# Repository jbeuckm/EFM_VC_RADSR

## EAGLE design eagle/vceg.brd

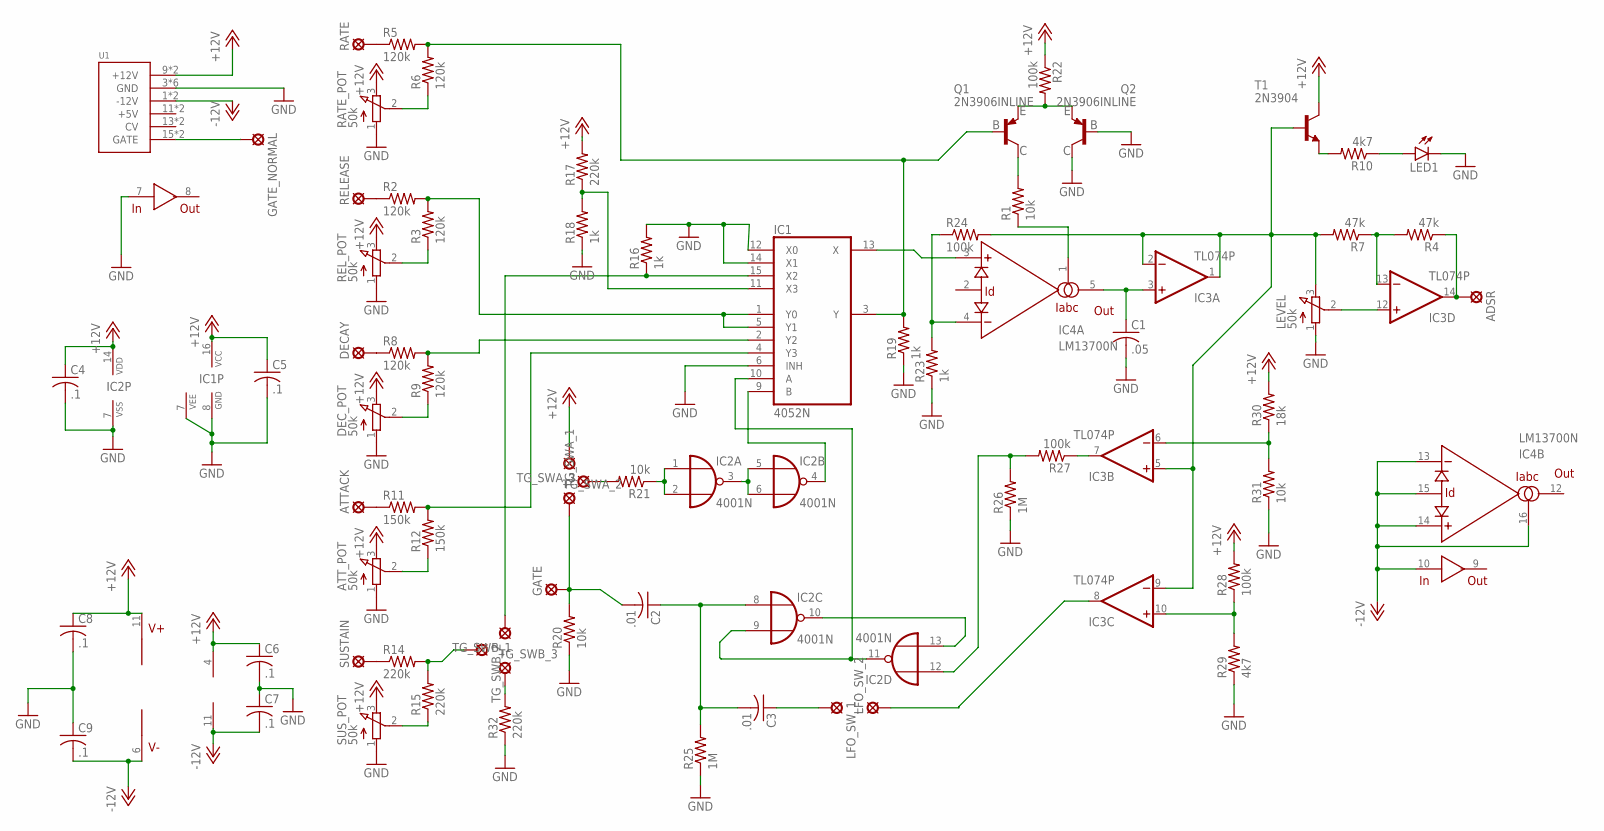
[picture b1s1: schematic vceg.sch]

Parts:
ADSR: LSP10
ATTACK: LSP10
ATT_POT: 50k; 3RP/1610N
C1: .05; C025-024X044
C2, C3: .01; C025-024X044
C4, C5, C6, C7, C8, C9: .1; C025-024X044
DECAY: LSP10
DEC_POT: 50k; 3RP/1610N
GATE: LSP10
GATE_NORMAL: LSP10
IC1: 4052N; DIL16
IC2: 4001N; DIL14
IC3: TL074P; DIL14
IC4: LM13700N; DIL16
LED1: LED5MM
LEVEL: 50k; 3RP/1610N
LFO_SW_1, LFO_SW_2: LSP10
Q1, Q2: 2N3906INLINE; TO92-CBE
R1, R20, R21, R31: 10k; AXIAL-0.4
R2, R3, R5, R6, R8, R9: 120k; AXIAL-0.4
R4, R7: 47k; AXIAL-0.4
R10, R29: 4k7; AXIAL-0.4
R11, R12: 150k; AXIAL-0.4
R14, R15, R17, R32: 220k; AXIAL-0.4
R16, R18, R19, R23: 1k; AXIAL-0.4
R22, R24, R27, R28: 100k; AXIAL-0.4
R25, R26: 1M; AXIAL-0.4
R30: 18k; AXIAL-0.4
RATE: LSP10
RATE_POT: 50k; 3RP/1610N
RELEASE: LSP10
REL_POT: 50k; 3RP/1610N
SUSTAIN: LSP10
SUS_POT: 50k; 3RP/1610N
T1: 2N3904; TO92
TG_SWA_1, TG_SWA_2, TG_SWA_3: LSP10
TG_SWB_1, TG_SWB_2, TG_SWB_3: LSP10
U1: POWER; POWER_16

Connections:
+12V: ATT_POT.3 (E), C4.1, C5.1, C6.1, C8.1, DEC_POT.3 (E), IC1.16 (VCC), IC2.14 (VDD), IC3.4 (V+), IC4.11 (V+), R17.P$2 (2), R22.P$1 (1), R28.P$2 (2), R30.P$2 (2), RATE_POT.3 (E), REL_POT.3 (E), SUS_POT.3 (E), T1.1 (C), TG_SWA_3.MP, U1.9 (+12V), U1.10 (+12V)
-12V: C7.2, C9.2, IC3.11 (V-), IC4.6 (V-), IC4.10 (IN), IC4.13 (-IN), IC4.14 (+IN), IC4.15 (ID), IC4.16 (IABC), U1.1 (-12V), U1.2 (-12V)
GND: ATT_POT.1 (A), C1.2, C4.2, C5.2, C6.2, C7.1, C8.2, C9.1, DEC_POT.1 (A), IC1.6 (INH), IC1.7 (VEE), IC1.8 (GND), IC1.12 (X0), IC1.14 (X1), IC2.7 (VSS), IC4.7 (IN), LED1.K (C), LEVEL.1 (A), Q2.B, Q2.C, R16.P$2 (2), R18.P$1 (1), R19.P$1 (1), R20.P$1 (1), R23.P$1 (1), R25.P$1 (1), R26.P$1 (1), R29.P$1 (1), R31.P$1 (1), R32.P$1 (1), RATE_POT.1 (A), REL_POT.1 (A), SUS_POT.1 (A), U1.3 (GND), U1.4 (GND), U1.5 (GND), U1.6 (GND), U1.7 (GND), U1.8 (GND)
unnamed: R2.P$1 (1), RELEASE.MP
unnamed: IC1.1 (Y0), IC1.5 (Y1), R2.P$2 (2), R3.P$2 (2)
unnamed: R3.P$1 (1), REL_POT.2 (S)
unnamed: R5.P$1 (1), RATE.MP
unnamed: IC1.3 (Y), Q1.B, R5.P$2 (2), R6.P$2 (2), R19.P$2 (2)
unnamed: R6.P$1 (1), RATE_POT.2 (S)
unnamed: DECAY.MP, R8.P$1 (1)
unnamed: IC1.2 (Y2), R8.P$2 (2), R9.P$2 (2)
unnamed: DEC_POT.2 (S), R9.P$1 (1)
unnamed: ATTACK.MP, R11.P$1 (1)
unnamed: IC1.4 (Y3), R11.P$2 (2), R12.P$2 (2)
unnamed: ATT_POT.2 (S), R12.P$1 (1)
unnamed: R14.P$1 (1), SUSTAIN.MP
unnamed: IC1.15 (X2), R16.P$1 (1), TG_SWB_1.MP
unnamed: R15.P$1 (1), SUS_POT.2 (S)
unnamed: IC1.11 (X3), R17.P$1 (1), R18.P$2 (2)
unnamed: IC1.10 (A), IC2.9 (I1), IC2.11 (O)
unnamed: IC2.1 (I0), IC2.2 (I1), R21.P$1 (1)
unnamed: IC2.3 (O), IC2.5 (I0), IC2.6 (I1)
unnamed: IC1.9 (B), IC2.4 (O)
unnamed: Q1.C, R1.P$2 (2)
unnamed: Q1.E, Q2.E, R22.P$2 (2)
unnamed: GATE_NORMAL.MP, U1.15 (GATE), U1.16 (GATE)
unnamed: IC4.4 (-IN), R23.P$2 (2), R24.P$1 (1)
unnamed: C2.1, C3.2, IC2.8 (I0), R25.P$2 (2)
unnamed: IC3.1 (OUT), IC3.2 (-IN), IC3.5 (+IN), IC3.9 (-IN), LEVEL.3 (E), R7.P$2 (2), R24.P$2 (2), T1.2 (B)
unnamed: C2.2, GATE.MP, R20.P$2 (2), TG_SWA_2.MP
unnamed: C1.1, IC3.3 (+IN), IC4.5 (OUT)
unnamed: IC3.7 (OUT), R27.P$1 (1)
unnamed: IC2.10 (O), IC2.13 (I1)
unnamed: IC2.12 (I0), R26.P$2 (2), R27.P$2 (2)
unnamed: IC3.8 (OUT), LFO_SW_2.MP
unnamed: IC3.6 (-IN), R30.P$1 (1), R31.P$2 (2)
unnamed: IC3.10 (+IN), R28.P$1 (1), R29.P$2 (2)
unnamed: C3.1, LFO_SW_1.MP
unnamed: R14.P$2 (2), R15.P$2 (2), TG_SWB_2.MP
unnamed: R32.P$2 (2), TG_SWB_3.MP
unnamed: R21.P$2 (2), TG_SWA_1.MP
unnamed: IC4.1 (IABC), R1.P$1 (1)
unnamed: IC3.12 (+IN), LEVEL.2 (S)
unnamed: IC1.13 (X), IC4.3 (+IN)
unnamed: ADSR.MP, IC3.14 (OUT), R4.P$1 (1)
unnamed: IC3.13 (-IN), R4.P$2 (2), R7.P$1 (1)
unnamed: R10.P$2 (2), T1.3 (E)
unnamed: LED1.A, R10.P$1 (1)

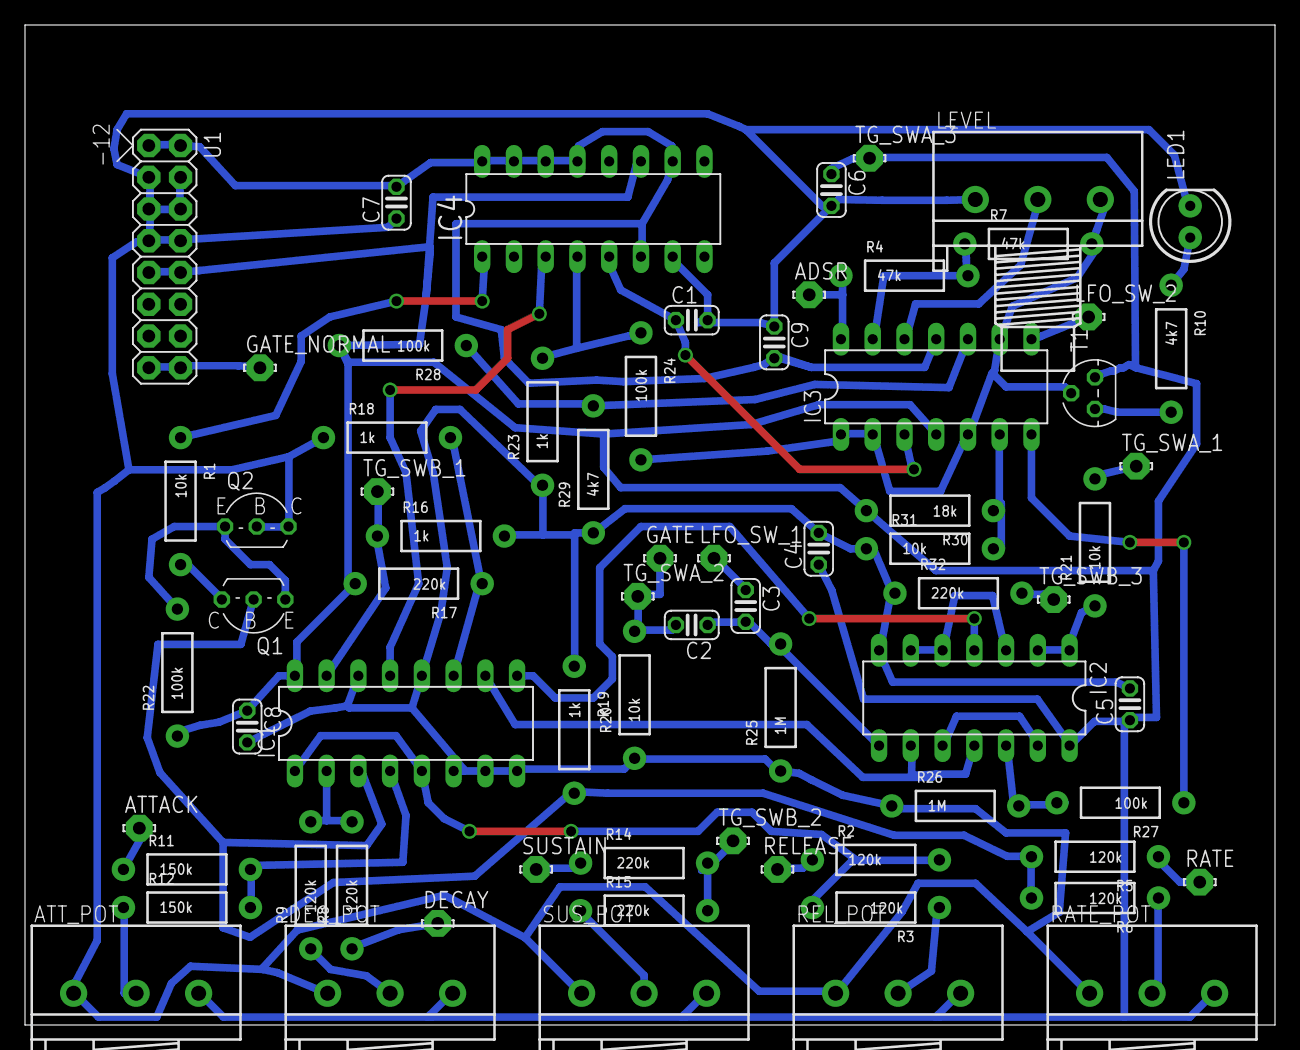
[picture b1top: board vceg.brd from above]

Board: 2 copper layers, 100.0 x 80.0 mm, 71 parts (0 on the bottom side), 48 nets.

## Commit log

2015-03-18 initial swing at the schematic
2015-03-18 starting on a board
2015-03-18 down to one flyer
2015-03-18 remembered to power tl074
2015-03-19 ca3080 with power now
2015-03-20 decoupling caps
2015-03-20 started board over
2015-03-21 completed layout with five flyers
2015-03-21 gcode for first prototype
2015-03-21 fixed schematic and board for 10k between 3906 and 3080
2015-03-21 updated gcode from fixed layout
2015-03-22 regenerated gcode
2015-03-28 lm13700 subbed and offset mixer added
2015-03-28 layout for lm13700 and offset amp
2015-03-28 layout with output indicator led
2015-03-28 improved layout
2015-04-01 updated panel to include trig gate switch

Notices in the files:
parts and their libraries:
SparkFun-Resistors: Licensing: Creative Commons ShareAlike 4.0 International - https://creativecommons.org/licenses/by-sa/4.0
